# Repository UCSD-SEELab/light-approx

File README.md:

# light-approx

light-approx
  - machine-learning
    - src
    - data
    - output
  - sensor-station
    - src
    - design
  - sensor-trinket
    - src
    - design
  - feature-extraction
    - sdsc-weather
      - src
      - data
    - gps-context
      - src
      - data

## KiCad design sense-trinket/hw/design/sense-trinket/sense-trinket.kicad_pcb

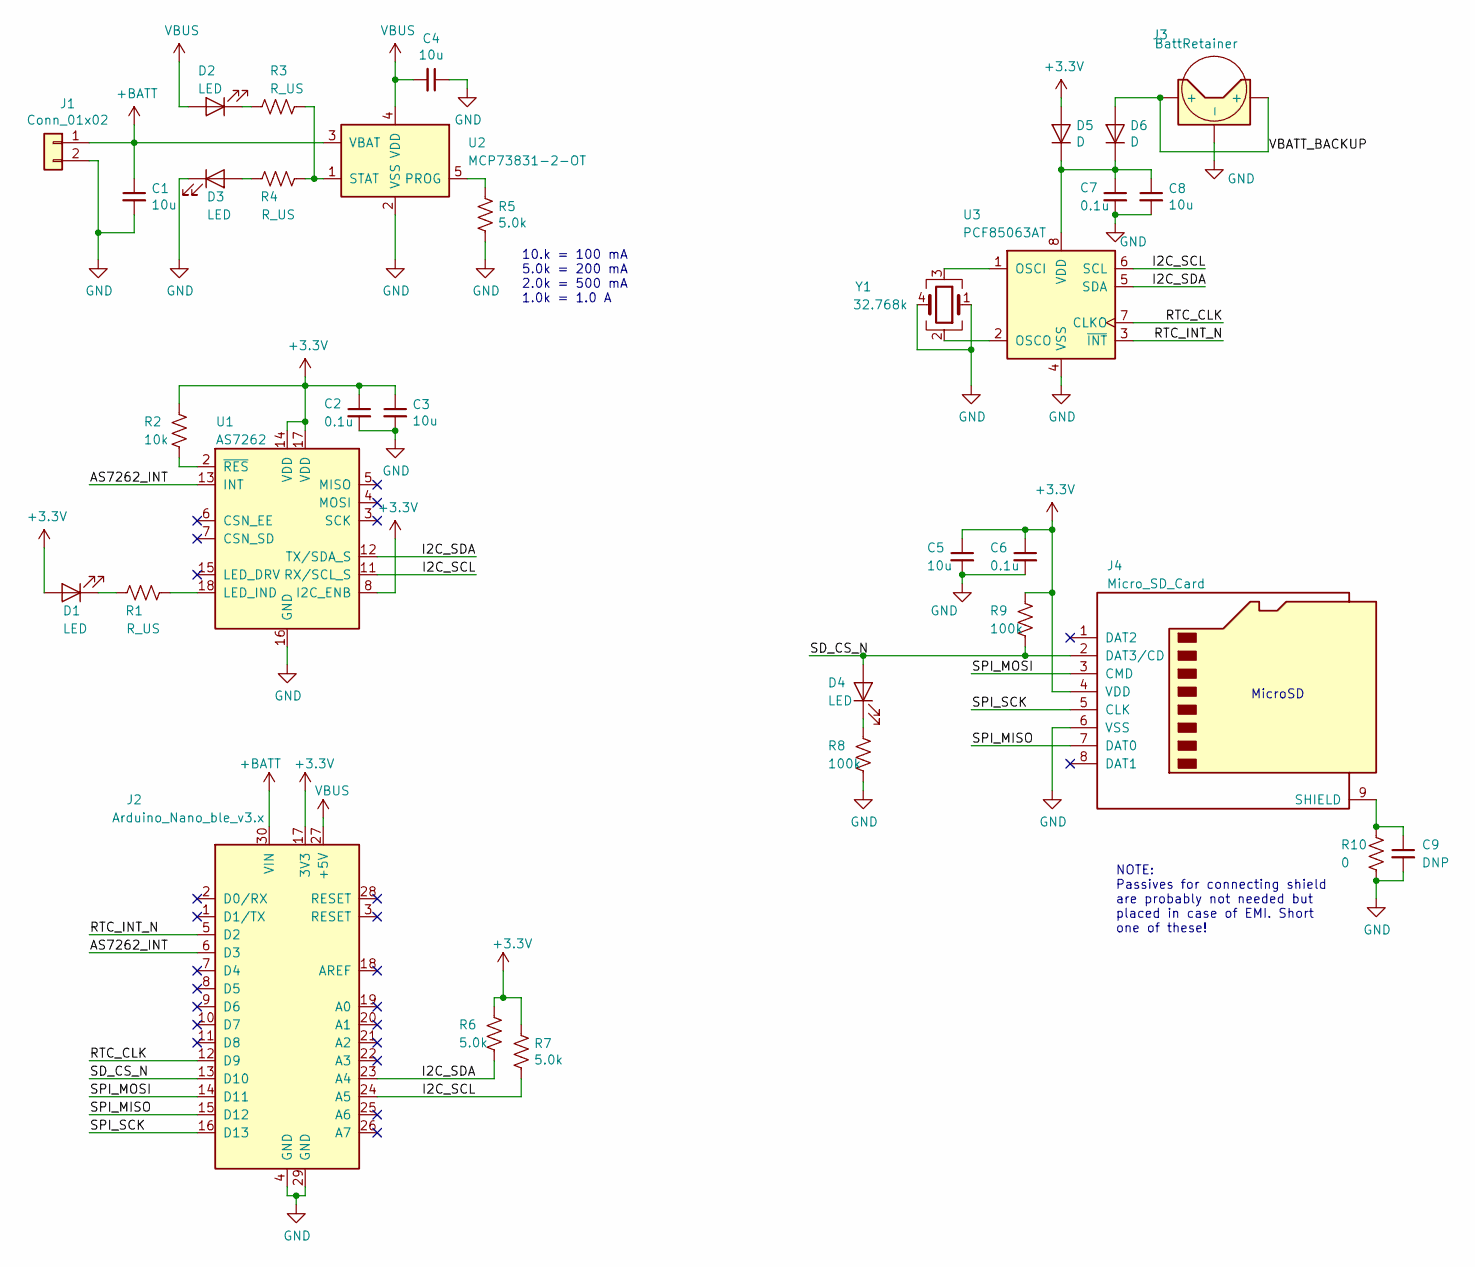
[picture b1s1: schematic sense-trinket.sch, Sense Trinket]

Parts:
C1, C3, C4, C5, C8: 10u; C_0805_2012Metric_Pad1.15x1.40mm_HandSolder
C2, C6, C7: 0.1u; C_0805_2012Metric_Pad1.15x1.40mm_HandSolder
C9: DNP; C_0805_2012Metric_Pad1.15x1.40mm_HandSolder
D1, D2, D3, D4: LED; LED_1206_3216Metric_Pad1.42x1.75mm_HandSolder
D5, D6: D; LED_1206_3216Metric_Pad1.42x1.75mm_HandSolder
J1: Conn_01x02; JST_socket_2pin_horizontal
J2: Arduino_Nano_ble_v3.x; Arduino_Nano
J3: BattRetainer; COIN_CELL_S8201R
J4: Micro_SD_Card; sd_molex_1051620001
R1, R3, R4: R_US; R_0805_2012Metric_Pad1.15x1.40mm_HandSolder
R2: 10k; R_0805_2012Metric_Pad1.15x1.40mm_HandSolder
R5, R6, R7: 5.0k; R_0805_2012Metric_Pad1.15x1.40mm_HandSolder
R8, R9: 100k; R_0805_2012Metric_Pad1.15x1.40mm_HandSolder
R10: 0; R_0805_2012Metric_Pad1.15x1.40mm_HandSolder
U1: AS7262; AMS_LGA-20_4.7x4.5mm_P0.65mm_handsolder
U2: MCP73831-2-OT; SOT-23-5_HandSoldering
U3: PCF85063AT; SOIC-8_3.9x4.9mm_P1.27mm
Y1: 32.768k; XTL_4pin_MC-146

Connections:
+3V3: C2.1, C3.1, C5.1, C6.1, D1.2 (A), D5.2 (A), J2.17 (3V3), J4.4 (VDD), R2.1, R6.1, R7.1, R9.1, U1.8 (I2C_ENB), U1.14 (VDD), U1.17 (VDD)
+BATT: C1.1, J1.1, J2.30 (VIN), U2.3 (VBAT)
/AS7262_INT: J2.6 (D3), U1.13 (INT)
/I2C_SCL: J2.24 (A5), R7.2, U1.11 (RX/SCL_S), U3.6 (SCL)
/I2C_SDA: J2.23 (A4), R6.2, U1.12 (TX/SDA_S), U3.5 (SDA)
/RTC_CLK: J2.12 (D9), U3.7 (CLKO)
/RTC_INT_N: J2.5 (D2), U3.3 (~INT~)
/SD_CS_N: D4.2 (A), J2.13 (D10), J4.2 (DAT3/CD), R9.2
/SPI_MISO: J2.15 (D12), J4.7 (DAT0)
/SPI_MOSI: J2.14 (D11), J4.3 (CMD)
/SPI_SCK: J2.16 (D13), J4.5 (CLK)
/VBATT_BACKUP: D6.2 (A), J3.1 (+), J3.2 (+)
GND: C1.2, C2.2, C3.2, C4.1, C5.2, C6.2, C7.2, C8.2, C9.2, D3.1 (K), J1.2, J2.4 (GND), J2.29 (GND), J3.3 (-), J4.6 (VSS), R5.2, R8.2, R10.2, U1.16 (GND), U2.2 (VSS), U3.4 (VSS), Y1.1, Y1.4
unnamed: C7.1, C8.1, D5.1 (K), D6.1 (K), U3.8 (VDD)
unnamed: C9.1, J4.9 (SHIELD), R10.1
unnamed: D1.1 (K), R1.2
unnamed: D2.1 (K), R3.2
unnamed: D3.2 (A), R4.2
unnamed: D4.1 (K), R8.1
unnamed: R1.1, U1.18 (LED_IND)
unnamed: R2.2, U1.2 (~RES)
unnamed: R3.1, R4.1, U2.1 (STAT)
unnamed: R5.1, U2.5 (PROG)
unnamed: U3.1 (OSCI), Y1.3
unnamed: U3.2 (OSCO), Y1.2
VBUS: C4.2, D2.2 (A), J2.27 (+5V), U2.4 (VDD)

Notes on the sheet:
10.k = 100 mA 5.0k = 200 mA 2.0k = 500 mA 1.0k = 1.0 A
NOTE: Passives for connecting shield are probably not needed but placed in case of EMI. Short one of these!
MicroSD

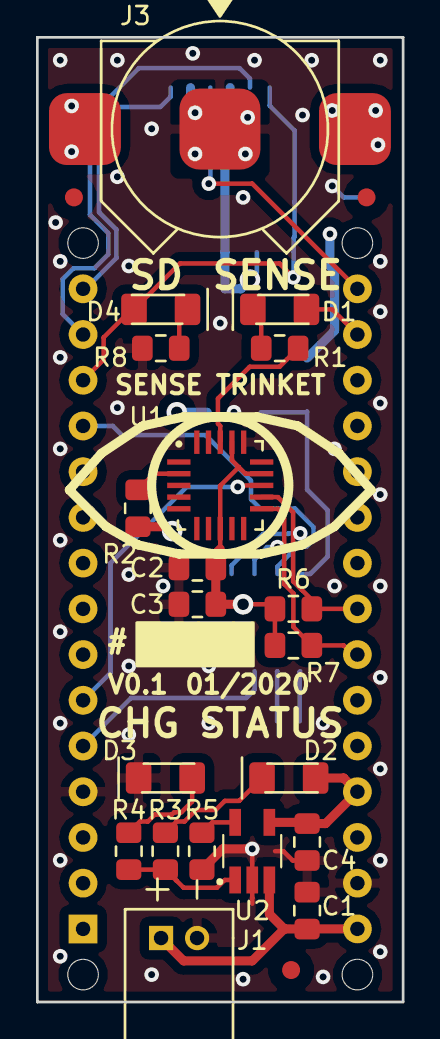
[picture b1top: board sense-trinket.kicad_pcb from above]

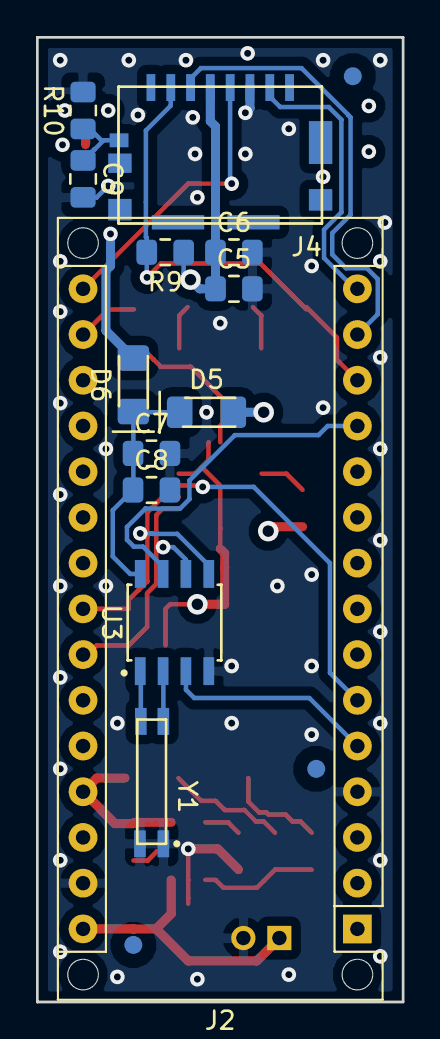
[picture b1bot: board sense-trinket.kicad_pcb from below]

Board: 4 copper layers, 20.3 x 53.6 mm, 33 parts (13 on the bottom side), 26 nets.

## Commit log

2019-10-08 Updated README.md with intended file structure
2019-10-08 Updated folder structure
2019-10-13 move code into new folder
2019-10-15 Add GPS OSM script and stationary script
2019-10-21 fixed stationary script -- need debug for config script
2019-10-21 configured second RPi, fixed absolute path for config.ini
2019-10-22 migrate away from ipython, save model as loadable file
2019-10-22 comment code
2019-10-23 chaneg weather processing file to py format
2019-10-28 auto process and combine data
2019-10-28 remove old model file
2019-10-28 new model draft
2019-10-29 increase more outdoor data points, increase clf acc
2019-10-29 confusion matrix and clf result
2019-10-29 Updated read/write paths to utilize script location
2020-01-16 model validatio using another researcher's data
2020-01-16 model result
2020-01-16 error in dataset representation fixed
2020-01-30 colocated data second validation
2020-01-30 sense-trinket v0.1 HW design
2020-02-06 add outliers plot and correponding code
2020-02-28 Added schematic for sense-trinket v0.1
2020-02-28 Added pseudocode for sense-trinket software
2020-03-03 fix the change of link and update of python3 library
2020-03-03 add more
2020-03-04 osm.py
2020-03-05 weather stationary validation
2020-03-06 change gaussian function
2020-03-06 fix errors
2020-03-06 photoreceptor function
2020-03-10 add end to end model
2020-04-14 basic sense-tricket script
2020-04-15 make code more modular and readable
2020-06-24 try LSTM model structure
2020-06-24 syntax error
